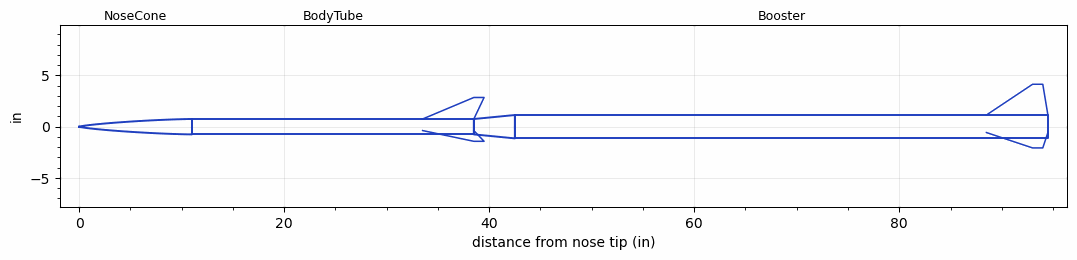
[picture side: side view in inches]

<RASAeroDocument>
 <FileVersion>2</FileVersion>
 <RocketDesign>
  <NoseCone>
   <Length>11</Length>
   <Diameter>1.5</Diameter>
   <Shape>Von Karman Ogive</Shape>
   <Location>0</Location>
  </NoseCone>
  <BodyTube>
   <Length>27.5</Length>
   <Diameter>1.5</Diameter>
   <Location>11</Location>
   <Fin>
    <Count>3</Count>
    <Chord>5</Chord>
    <Span>2.1</Span>
    <SweepDistance>5</SweepDistance>
    <TipChord>1</TipChord>
    <Thickness>0.1</Thickness>
    <Location>5</Location>
    <AirfoilSection>Biconvex</AirfoilSection>
   </Fin>
  </BodyTube>
  <Booster>
   <Length>52</Length>
   <Diameter>2.277</Diameter>
   <InsideDiameter>1.5</InsideDiameter>
   <Location>38.5</Location>
   <ShoulderLength>4</ShoulderLength>
   <Fin>
    <Count>3</Count>
    <Chord>6</Chord>
    <Span>3</Span>
    <SweepDistance>4.5</SweepDistance>
    <TipChord>1</TipChord>
    <Thickness>0.1</Thickness>
    <LERadius>0.02</LERadius>
    <Location>6</Location>
    <AirfoilSection>Biconvex</AirfoilSection>
   </Fin>
  </Booster>
  <Surface>Smooth Paint</Surface>
  <ModifiedBarrowman>False</ModifiedBarrowman>
  <Turbulence>False</Turbulence>
  <UseBooster1>False</UseBooster1>
  <UseBooster2>False</UseBooster2>
 </RocketDesign>
 <LaunchSite>
  <Altitude>3900</Altitude>
  <Pressure>0</Pressure>
  <RodAngle>0</RodAngle>
  <RodLength>12</RodLength>
  <Temperature>70</Temperature>
  <WindSpeed>8</WindSpeed>
 </LaunchSite>
 <Recovery>
  <Altitude1>1000</Altitude1>
  <Altitude2>700</Altitude2>
  <DeviceType1>Parachute</DeviceType1>
  <DeviceType2>Parachute</DeviceType2>
  <Event1>True</Event1>
  <Event2>True</Event2>
  <Size1>5</Size1>
  <Size2>30</Size2>
  <EventType1>Apogee</EventType1>
  <EventType2>Altitude</EventType2>
  <CD1>1.33</CD1>
  <CD2>1.33</CD2>
 </Recovery>
 <SimulationList>
  <Simulation>
   <SustainerEngine>K627LR  (Loki)</SustainerEngine>
   <SustainerLaunchWt>3</SustainerLaunchWt>
   <SustainerNozzleDiameter>0.9</SustainerNozzleDiameter>
   <SustainerCG>24</SustainerCG>
   <SustainerIgnitionDelay>0</SustainerIgnitionDelay>
   <Booster1SeparationDelay>0</Booster1SeparationDelay>
   <Booster1IgnitionDelay>0</Booster1IgnitionDelay>
   <IncludeBooster1>False</IncludeBooster1>
   <Booster2Delay>0</Booster2Delay>
   <IncludeBooster2>False</IncludeBooster2>
   <TimetoApogee>37.17977</TimetoApogee>
   <MaxAltitude>37596.47</MaxAltitude>
   <MaxVelocity>4155.457</MaxVelocity>
  </Simulation>
  <Simulation>
   <SustainerEngine>K627LR  (Loki)</SustainerEngine>
   <SustainerLaunchWt>3.5</SustainerLaunchWt>
   <SustainerNozzleDiameter>0.9</SustainerNozzleDiameter>
   <SustainerCG>24</SustainerCG>
   <SustainerIgnitionDelay>22</SustainerIgnitionDelay>
   <Booster1Engine>M1350W  (AT)</Booster1Engine>
   <Booster1LaunchWt>14</Booster1LaunchWt>
   <Booster1SeparationDelay>0</Booster1SeparationDelay>
   <Booster1IgnitionDelay>12</Booster1IgnitionDelay>
   <Booster1CG>60</Booster1CG>
   <Booster1NozzleDiameter>1.25</Booster1NozzleDiameter>
   <IncludeBooster1>True</IncludeBooster1>
   <Booster2Engine>M1350W  (AT)</Booster2Engine>
   <Booster2LaunchWt>17.7</Booster2LaunchWt>
   <Booster2Delay>0</Booster2Delay>
   <Booster2CG>80</Booster2CG>
   <Booster2NozzleDiameter>1.25</Booster2NozzleDiameter>
   <IncludeBooster2>True</IncludeBooster2>
   <MaxVelocity>14.67</MaxVelocity>
  </Simulation>
  <Simulation>
   <SustainerEngine>K627LR  (Loki)</SustainerEngine>
   <SustainerLaunchWt>3.5</SustainerLaunchWt>
   <SustainerNozzleDiameter>0.9</SustainerNozzleDiameter>
   <SustainerCG>24</SustainerCG>
   <SustainerIgnitionDelay>20</SustainerIgnitionDelay>
   <Booster1Engine>K627LR  (Loki)</Booster1Engine>
   <Booster1LaunchWt>7</Booster1LaunchWt>
   <Booster1SeparationDelay>0</Booster1SeparationDelay>
   <Booster1IgnitionDelay>0</Booster1IgnitionDelay>
   <Booster1CG>41</Booster1CG>
   <Booster1NozzleDiameter>0.9</Booster1NozzleDiameter>
   <IncludeBooster1>True</IncludeBooster1>
   <Booster2Delay>0</Booster2Delay>
   <IncludeBooster2>False</IncludeBooster2>
   <TimetoApogee>88.39993</TimetoApogee>
   <MaxAltitude>100727.4</MaxAltitude>
   <MaxVelocity>4016.819</MaxVelocity>
  </Simulation>
  <Simulation>
   <SustainerEngine>K627LR  (Loki)</SustainerEngine>
   <SustainerLaunchWt>3</SustainerLaunchWt>
   <SustainerNozzleDiameter>0.9</SustainerNozzleDiameter>
   <SustainerCG>24</SustainerCG>
   <SustainerIgnitionDelay>24</SustainerIgnitionDelay>
   <Booster1Engine>M1350W  (AT)</Booster1Engine>
   <Booster1LaunchWt>13.5</Booster1LaunchWt>
   <Booster1SeparationDelay>0</Booster1SeparationDelay>
   <Booster1IgnitionDelay>0</Booster1IgnitionDelay>
   <Booster1CG>60</Booster1CG>
   <Booster1NozzleDiameter>1.25</Booster1NozzleDiameter>
   <IncludeBooster1>True</IncludeBooster1>
   <Booster2Delay>0</Booster2Delay>
   <IncludeBooster2>False</IncludeBooster2>
   <TimetoApogee>166.5899</TimetoApogee>
   <MaxAltitude>347477.3</MaxAltitude>
   <MaxVelocity>5463.395</MaxVelocity>
  </Simulation>
 </SimulationList>
</RASAeroDocument>
